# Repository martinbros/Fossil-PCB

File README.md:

# Fossil PCB
 Animal Crossing Fossil PCB

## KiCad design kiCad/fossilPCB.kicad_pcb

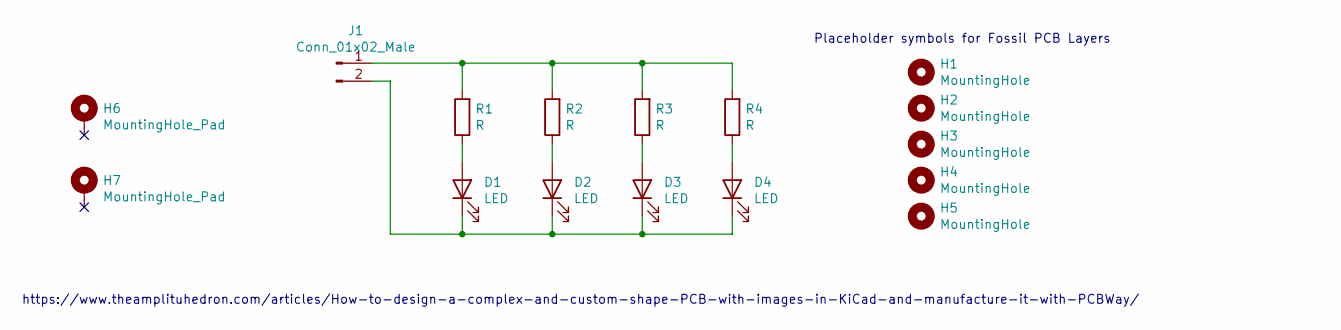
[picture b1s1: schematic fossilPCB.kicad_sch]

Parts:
D1, D2, D3, D4: LED; LED_2512_6332Metric_Pad1.52x3.35mm_HandSolder
H1: MountingHole; fossilCopperFill
H2: MountingHole; fossilEdge
H3: MountingHole; fossilMasklessBack
H4: MountingHole; fossilMasklessFront
H5: MountingHole; fossilSlikscreen
H6, H7: MountingHole_Pad; SMD_2x5mm
J1: Conn_01x02_Male; PinSocket_1x02_P2.54mm_Vertical
R1, R2, R3, R4: R; R_1210_3225Metric_Pad1.42x2.65mm_HandSolder

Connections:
unnamed: D1.1 (K), D2.1 (K), D3.1 (K), D4.1 (K), J1.2
unnamed: D1.2 (A), R1.1
unnamed: D2.2 (A), R2.1
unnamed: D3.2 (A), R3.1
unnamed: D4.2 (A), R4.1
unnamed: J1.1, R1.2, R2.2, R3.2, R4.2

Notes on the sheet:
https://www.theamplituhedron.com/articles/How-to-design-a-complex-and-custom-shape-PCB-with-images-in-KiCad-and-manufacture-it-with-PCBWay/
Placeholder symbols for Fossil PCB Layers

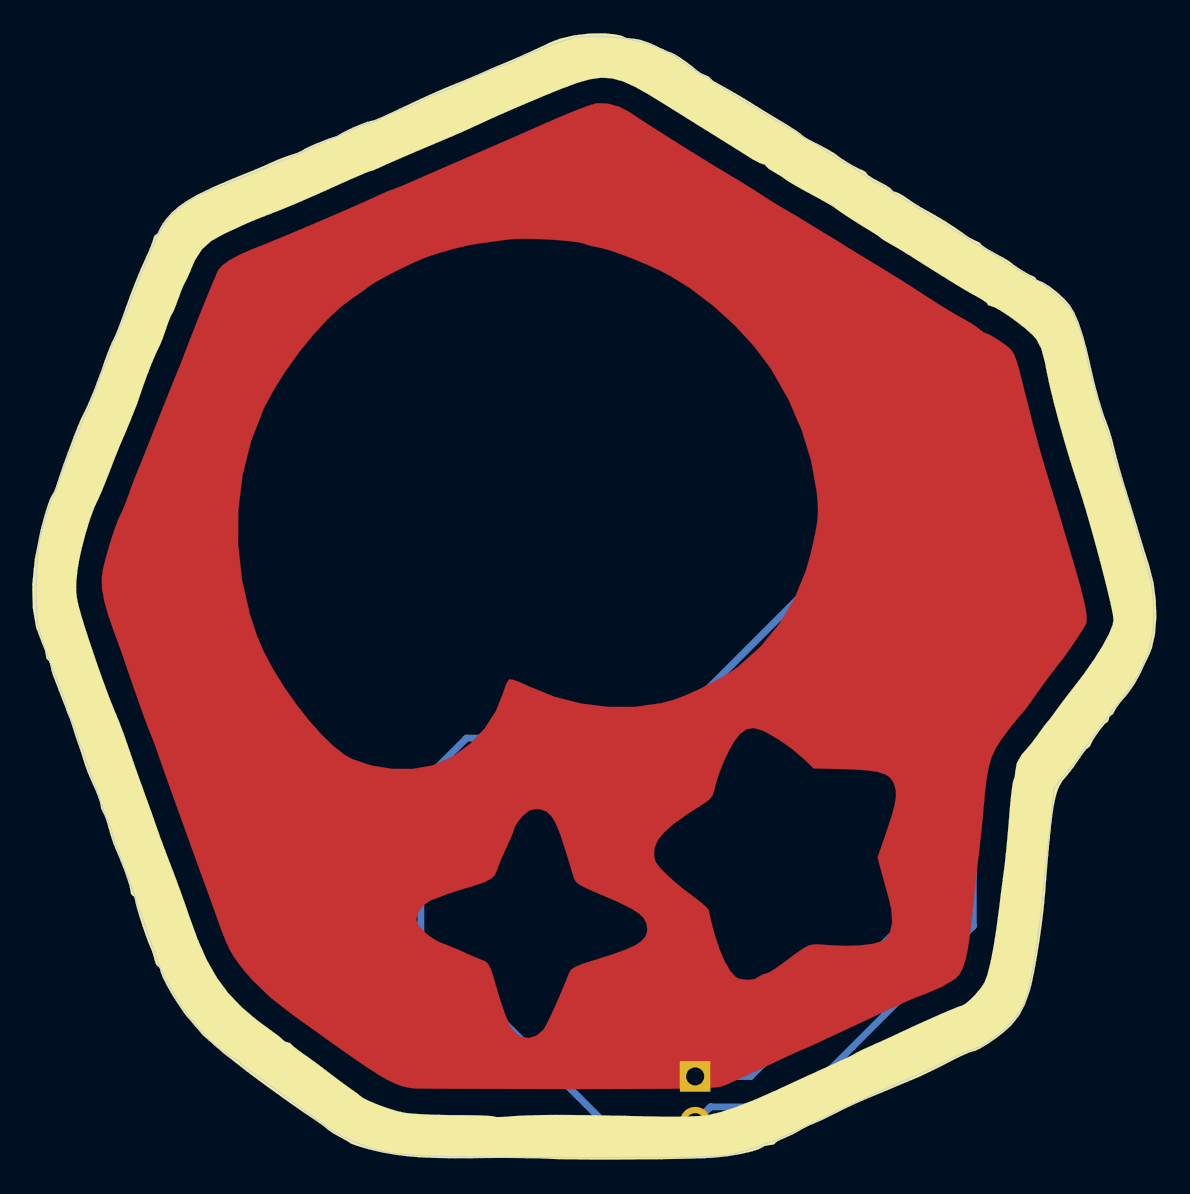
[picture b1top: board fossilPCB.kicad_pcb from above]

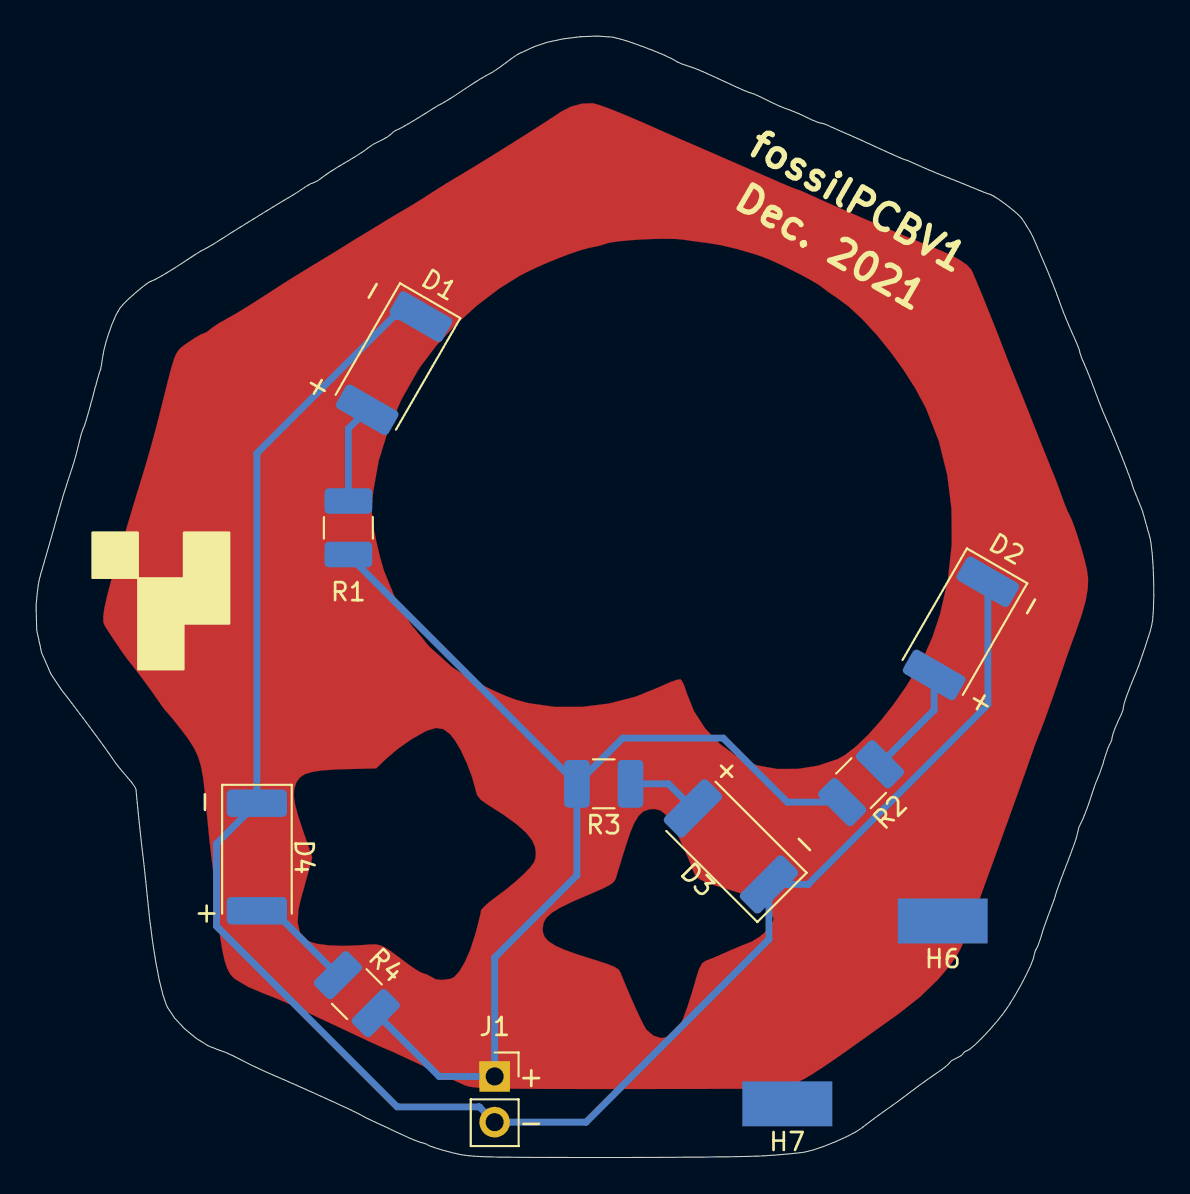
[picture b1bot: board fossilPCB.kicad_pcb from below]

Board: 2 copper layers, 62.1 x 62.3 mm, 16 parts (11 on the bottom side), 6 nets.

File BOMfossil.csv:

Symbol,Value,Mouser PN
"R1, R2, R3, R4",330,279-CRGCQ1210J330R
"D1, D2, D3, D4",~,593-VAOL-5701WY4

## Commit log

2025-01-23 Adding License
